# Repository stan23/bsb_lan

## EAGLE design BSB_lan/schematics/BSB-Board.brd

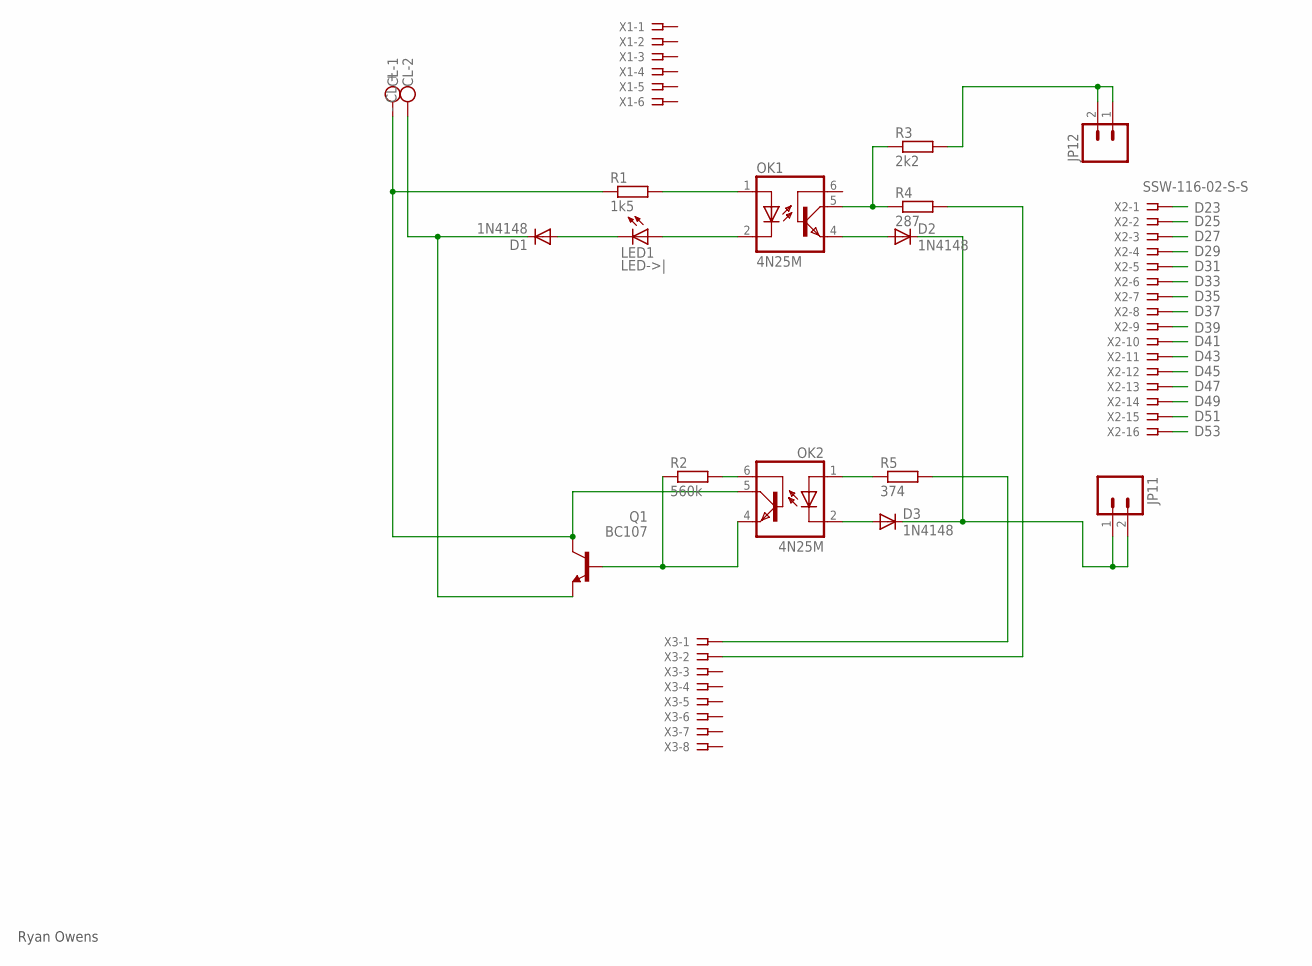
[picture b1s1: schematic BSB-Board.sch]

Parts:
CL: - CL +; W237-102
D1, D2, D3: 1N4148; DO35-7
JP11, JP12: M02LOCK; 1X02_LOCK
LED1: LED->|; LED2X5
OK1, OK2: 4N25M; DIL06
Q1: BC107; TO18
R1: 1k5; 0204/7
R2: 560k; 0207/10
R3: 2k2; 0204/7
R4: 287; 0204/7
R5: 374; 0204/7
X1: SSW-106-02-S-S
X2: SSW-116-02-S-S
X3: SSW-108-02-S-S

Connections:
A14: R4.2, X3.2
A15: R5.2, X3.1
D23: X2.1
D25: X2.2
D27: X2.3
D29: X2.4
D31: X2.5
D33: X2.6
D35: X2.7
D37: X2.8
D39: X2.9
D41: X2.10
D43: X2.11
D45: X2.12
D47: X2.13
D49: X2.14
D51: X2.15
D53: X2.16
GND: D2.C, D3.C, JP11.1, JP11.2
unnamed: OK1.1 (A), R1.2
unnamed: LED1.A, OK1.2 (C)
unnamed: OK2.6 (BAS), R2.2
unnamed: D1.A, LED1.K (C)
unnamed: OK2.4 (EMI), Q1.2 (B), R2.1
unnamed: CL.1, OK2.5 (COL), Q1.3 (C), R1.1
unnamed: CL.2, D1.C, Q1.1 (E)
unnamed: OK1.5 (COL), R3.1, R4.1
unnamed: D2.A, OK1.4 (EMI)
unnamed: OK2.1 (A), R5.1
unnamed: D3.A, OK2.2 (C)
unnamed: JP12.1, JP12.2, R3.2

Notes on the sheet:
Ryan Owens

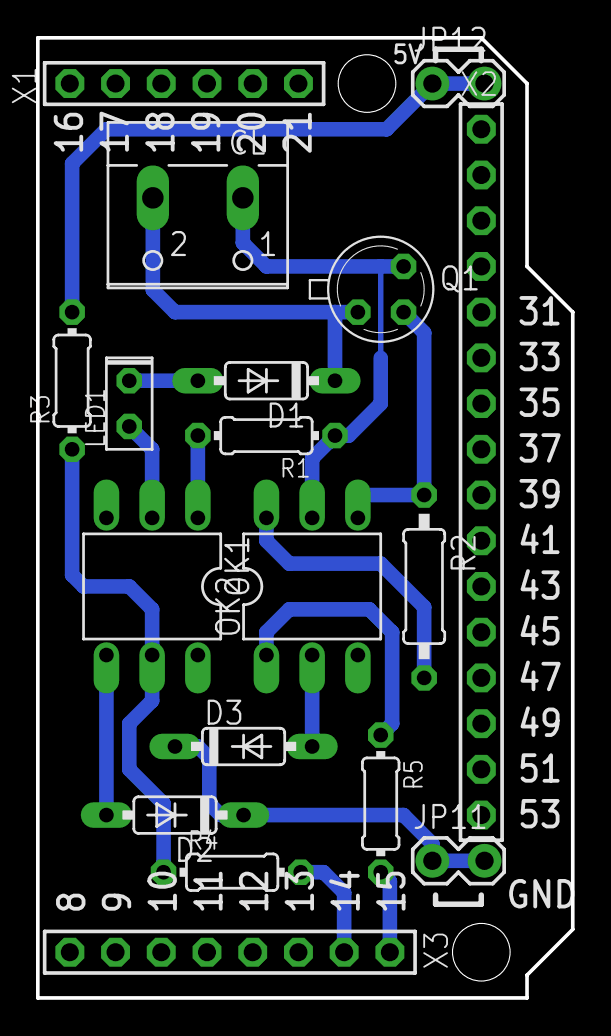
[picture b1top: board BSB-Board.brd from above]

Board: 2 copper layers, 29.7 x 53.3 mm, 18 parts (0 on the bottom side), 15 nets.

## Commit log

2017-03-23 Add files via upload
    Schematic:
    - fix ERC warnings in schematic (missing junctions - use NET instead of WIRE).
    Board:
    - rearrange components
    - use thicker wires
    - route single-sided
